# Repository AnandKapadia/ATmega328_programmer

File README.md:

AT Programming Shield
==========

##BOM
* Shield Board (eagle schematic provided)
* Arduino Uno
* Chip to Program, either an ATTiny85, ATmega328P-PU, ATmega328P(TQFP)
* 16Mhz Crystal
* Capacitors for Crytsal (22 pF) x2
* 10uF Cap 
* 10k Resistor (0603)
* 330 Resistor (0603)
* 4 Slide Switches
* SMD LED (1206)
For a detailed list please see the BOM

##Here is what the shield looks like. 

Image: 

Soldered: 

##How To Use
NOTE: You can only program one board at a time. 

From top to bottom, here is what each switch does. 
* Switch 1 (Connection to Pin 1 of ATMega): Arduino 10 <--> Arduino Reset
* Switch 2 (Connection to Pin 3 of ATMega): Disconnected <--> Arduino TX
* Switch 3 (Conenction to Pin 2 of ATMega): Disconnected <--> Arduino RX
* Switch 4 : Arduino Reset connected to Capacitor (10uF) <--> Disconnected

For ATtiny85: 
* Switches 1-3 : Does not matter
* Switch 4 : To the Left (Reset connected to Cap)

For Bootloader onto ATMega (both forms):
* Switch 1: To the left (Arduino 10)
* Switch 2/3: To the left (Disconnected)
* Switch 4: To the right (Disconnected)
    
For Programming onto ATMega (both forms):
* Switch 1: To the Right (Arduino Reset)
* Switch 2/3: To the Right (Rx/Tx)
* Switch 4: To the right (Disconnected)
* Note: Remove the arduino's built in mega chip to do this.

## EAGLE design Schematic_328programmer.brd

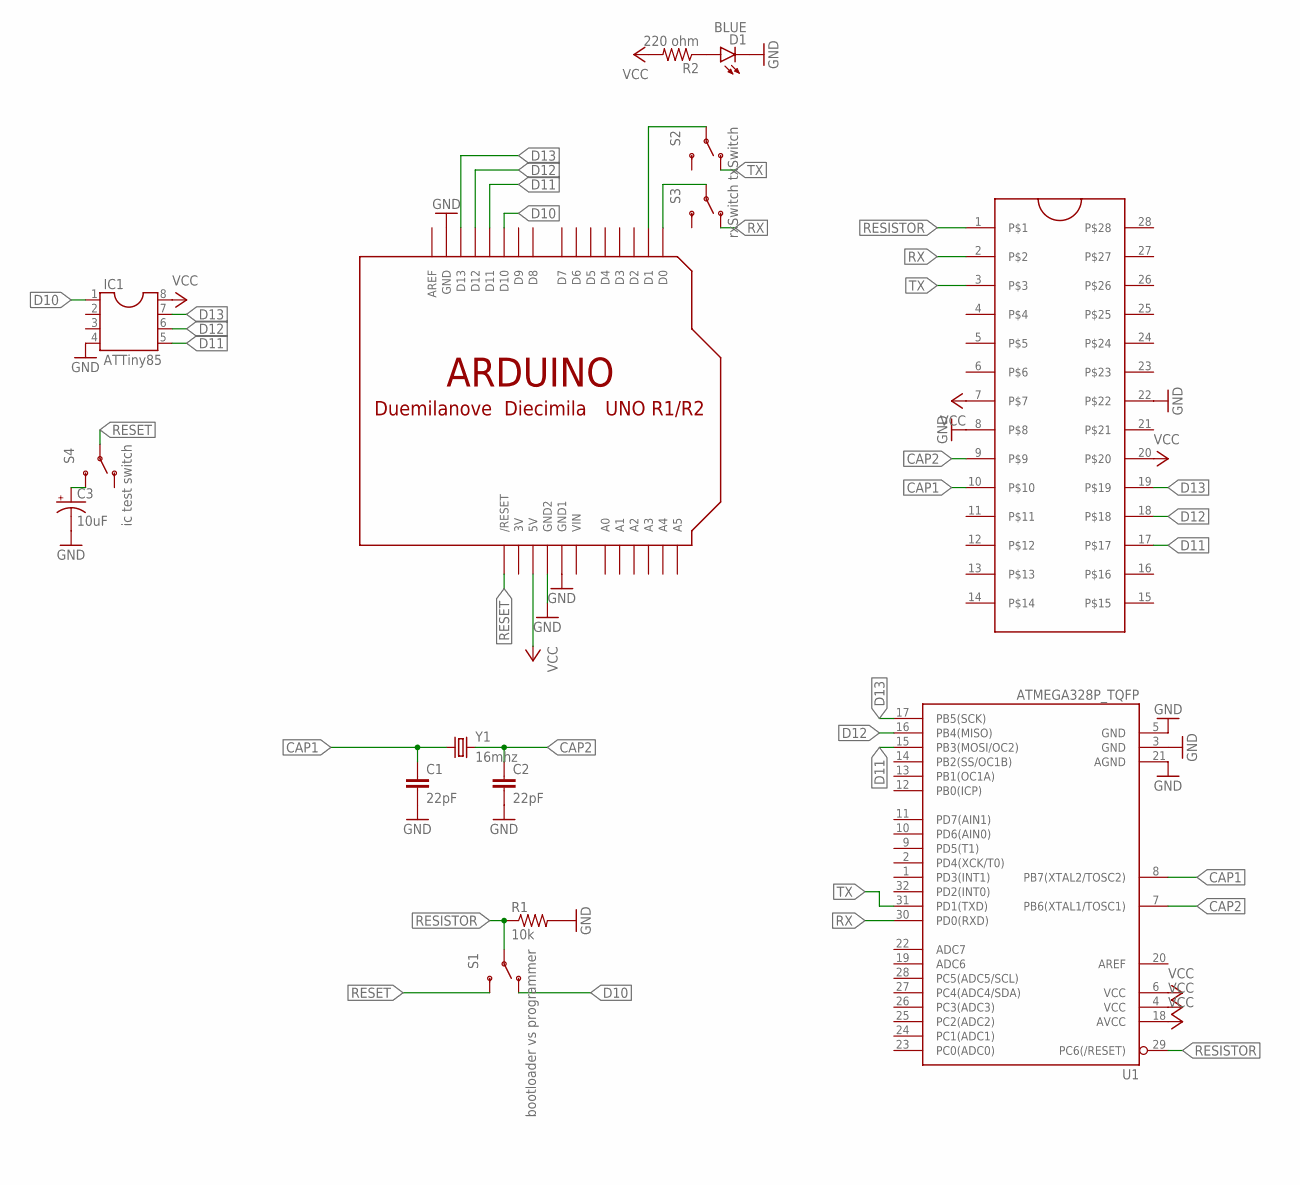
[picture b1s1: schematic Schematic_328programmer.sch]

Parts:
C1, C2: 22pF; 0603-CAP
C3: 10uF; CPOL-RADIAL-10UF-25V
D1: BLUE; LED-1206
IC1: ATTiny85; SOCKET-08
R1: 10k; 0603-RES
R2: 220 ohm; 0603-RES
S1: bootloader vs programmer; SWITCH-SPDT
S2: txSwitch; SWITCH-SPDT
S3: rxSwitch; SWITCH-SPDT
S4: ic test switch; SWITCH-SPDT
U1: ATMEGA328P_TQFP; TQFP32-08
U$1: ARDUINOUNO; ARDUINO
U$3: ZIFSOCKET-28-3ZIFFSOCKET-28-3; DIL28-3-ZIF_SOCKET
Y1: 16mhz; HC49US

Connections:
3V: U$1.3V
CAP1: C1.1, U1.8 (PB7(XTAL2/TOSC2)), U$3.10, Y1.1
CAP2: C2.1, U1.7 (PB6(XTAL1/TOSC1)), U$3.9, Y1.2
D10: IC1.1, S1.1 (O), U$1.D10
D11: IC1.5, U1.15 (PB3(MOSI/OC2)), U$1.D11, U$3.17
D12: IC1.6, U1.16 (PB4(MISO)), U$1.D12, U$3.18
D13: IC1.7, U1.17 (PB5(SCK)), U$1.D13, U$3.19
GND: C1.2, C2.2, C3.2 (-), D1.C, IC1.4, R1.2, U1.3 (GND), U1.5 (GND), U1.21 (AGND), U$1.GND, U$1.GND1, U$1.GND2, U$3.8, U$3.22
unnamed: D1.A, R2.1
unnamed: S3.2, U$1.D0
unnamed: S2.2, U$1.D1
unnamed: C3.1 (+), S4.3 (S)
RESET: S1.3 (S), S4.2, U$1.RESET (/RESET)
RESISTOR: R1.1, S1.2, U1.29 (PC6(/RESET)), U$3.1
RX: S3.1 (O), U1.30 (PD0(RXD)), U$3.2
TX: S2.1 (O), U1.31 (PD1(TXD)), U$3.3
VCC: IC1.8, R2.2, U1.4 (VCC), U1.6 (VCC), U1.18 (AVCC), U$1.5V, U$3.7, U$3.20
VIN: U$1.VIN

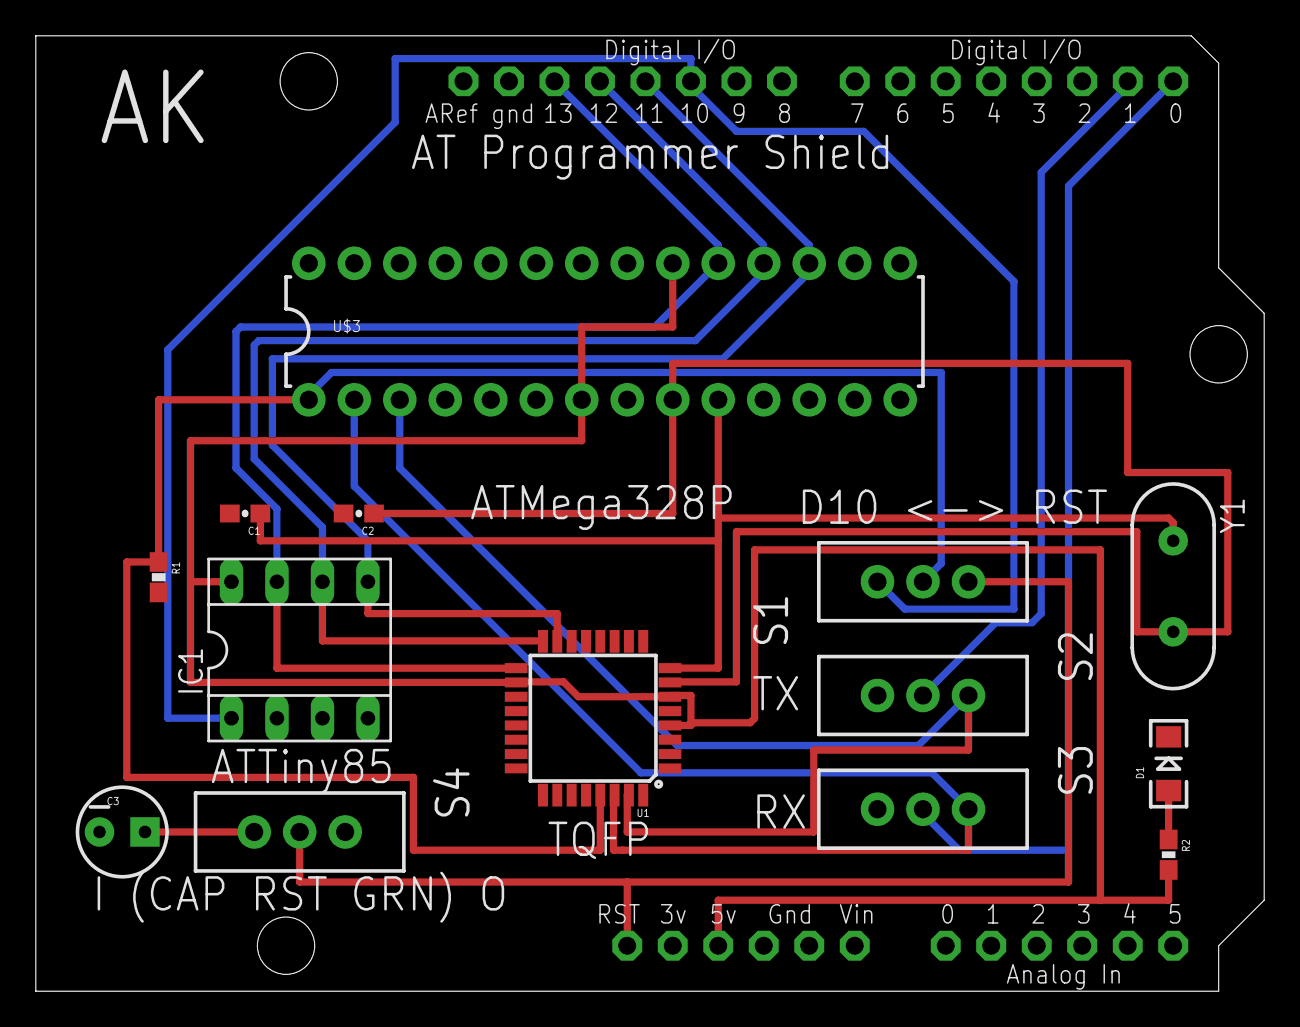
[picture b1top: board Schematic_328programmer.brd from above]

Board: 2 copper layers, 68.6 x 53.3 mm, 15 parts (0 on the bottom side), 16 nets.

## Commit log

2016-05-25 Uploaded Eagle Board and Schematic
    Sparkfun and Adafruit libraries were used in this project.
2016-06-08 Images Added, Eagle Libraries
2016-06-08 Updated Board CAD files
2016-06-08 Readme Updated
2016-06-08 Bullet Format Updated

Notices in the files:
parts and their libraries:
SparkFun-Capacitors: Licensing: Creative Commons ShareAlike 4.0 International - https://creativecommons.org/licenses/by-sa/4.0
